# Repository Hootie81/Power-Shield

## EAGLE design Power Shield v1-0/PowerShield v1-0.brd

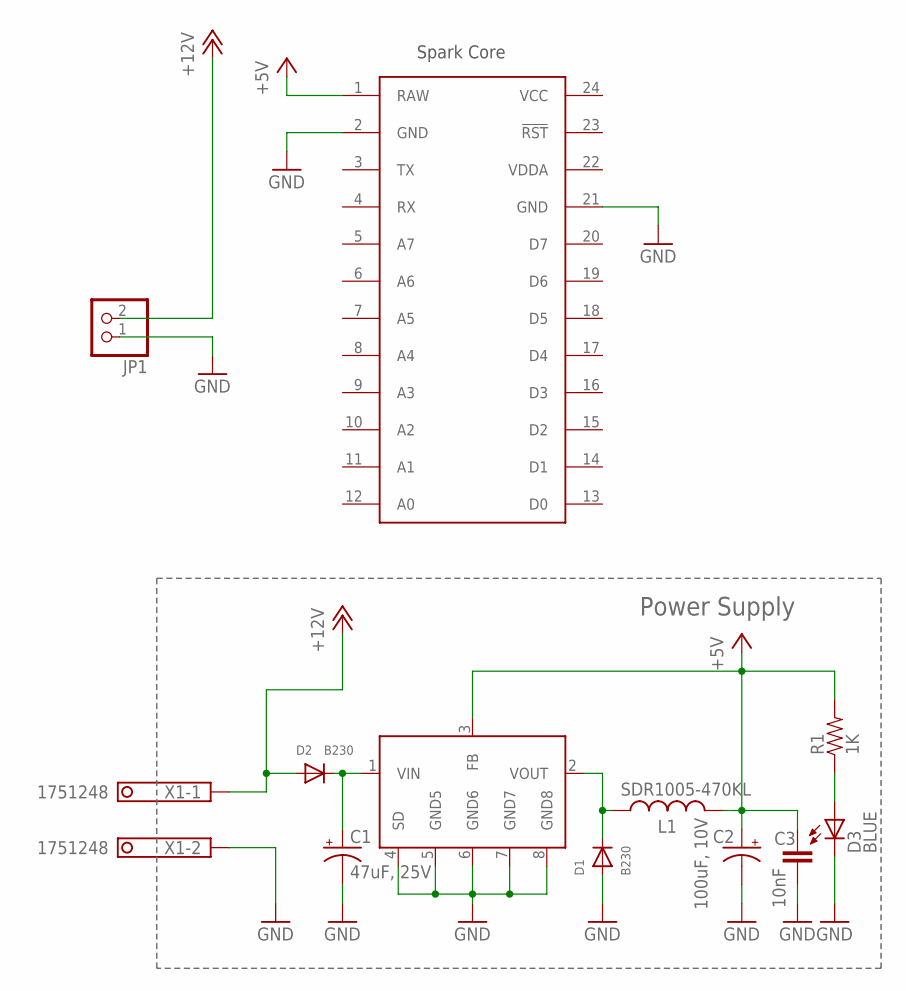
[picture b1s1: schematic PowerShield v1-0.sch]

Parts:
C1: 47uF, 25V; PANASONIC_D
C2: 100uF, 10V; PANASONIC_D
C3: 10nF; 0603-CAP
D1, D2: B230; SMADIODE
D3: BLUE; LED-0603
JP1: PINHD-1X2; 1X02
L1: SDR1005-470KL; INDUCTOR-SDR1005-470KL
R1: 1K; 0603-RES
U1: AP1509-50SG-13; SO08
U$2: SPARK_CORECORE; SPARK_CORE
X1: 1751248

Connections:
+5V: C2.+, C3.2, L1.P$2 (2), R1.2, U1.3 (FB), U$2.1 (RAW)
+12V: D2.A, JP1.2, X1.1
GND: C1.-, C2.-, C3.1, D1.A, D3.C, JP1.1, U1.4 (SD), U1.5 (GND5), U1.6 (GND6), U1.7 (GND7), U1.8 (GND8), U$2.2 (GND), U$2.21 (GND), X1.2
unnamed: D3.A, R1.1
unnamed: C1.+, D2.C, U1.1 (VIN)
unnamed: D1.C, L1.P$1 (1), U1.2 (VOUT)
VCC: U$2.24 (VCC)
VDDA: U$2.22 (VDDA)

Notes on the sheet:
Power Supply
Spark Core

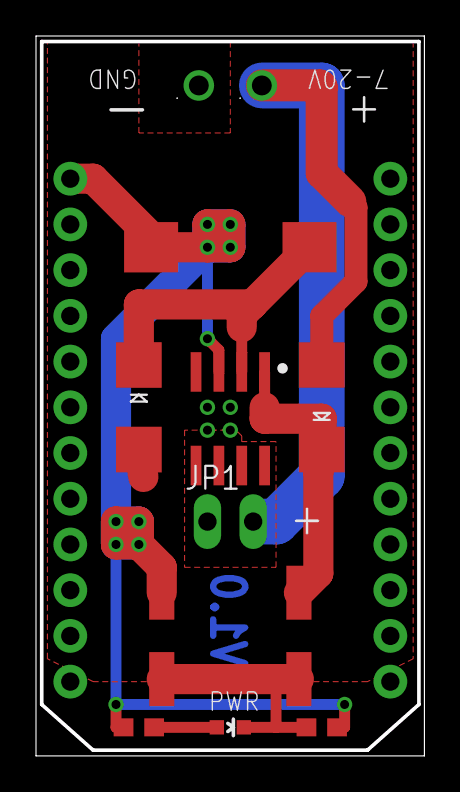
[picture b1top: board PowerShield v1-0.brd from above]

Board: 2 copper layers, 21.6 x 40.0 mm, 12 parts (0 on the bottom side), 6 nets.

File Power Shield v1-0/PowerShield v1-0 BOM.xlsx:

Hootie81's Power Shield
Version 1.0
41853
Description | Qty | Value | Package | Designator | Manufacturer | Part Number
PCB | 1 | V1.0 | NA | NA | OSH Park | NA
Diode Schottky | 2 | 30v 2A | DO-214AC | D1, D2 | Diodes inc | B230A-13-F
Inductor | 1 | 47uH | Non Standard | L1 | Bourns inc | SDR1005-470KL
Capacitor Aluminum | 1 | 100uf 35v | Radial Can, SMD | C2 | Panasonic | EEE-1AA101SP
Capacitor Aluminum | 1 | 47uF 35v | Radial Can, SMD | C1 | Panasonic | EEE-1EA470WP
IC REG BUCK | 1 | 5V 2A | 8SOIC | U1 | Diodes Inc | AP1509-50SG-13
Capacitor | 1 | 10nf, 10v, 10% | 603 | C3 | AVX Corp | 0603ZC103KAT2A
Resistor | 1 | 1K 0.25W 5% | 603 | R1 | Rohm Semiconductor | ESR03EZPJ102
Terminal Block | 1 | NA | NA | X1 | Phoenix Contact | 1751248
SIL Vert Pin header | 1 | 2 pin | NA 0.100" | JP1 | Harwin Inc | M20-9990246
LED blue | 1 | 3.4v 20mA | 603 | D3 | Lite-on Inc | LTST-C191TBKT

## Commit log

2014-07-26 5v Power supply board for Spark Core
    A power supply board for the spark core with a wide input voltage range
    of 7v to 22v, the footprint is similar to the Spark slightly longer for
    access to input terminal. I supplies a regulated 5v output at up to 2A
    for driving the spark and other devices.
    A header included near the centre of the board passes the input power to
    other boards that require the higher voltage
2014-07-28 Fixed silkscreen
    Fixed silkscreen
    Added Gerbers
2014-08-02 Added BOM
2014-09-12 Cleanup
    Removed old versions to avoid confusion

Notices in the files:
parts and their libraries:
SparkFun-Passives: Licensing: CC v3.0 Share-Alike You are welcome to use this library for commercial purposes.
